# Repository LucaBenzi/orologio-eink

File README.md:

# Orologio E-Ink

E-ink desk clock with a 3.7" display, ESP32-C3 and LiFePO4 battery. Connects to WiFi, syncs time via NTP and runs for about 2 years on a single ~2-hour USB-C charge.

**Philosophy:** "Place it and it works. Recharge it every 2 years."

## Features

- 3.7" e-ink display (240x416 px) — sunlight readable, zero power draw at rest
- ESP32-C3 in deep sleep (~5 µA), wakes up every minute to update the display
- External 32.768 kHz crystal for accurate deep-sleep timekeeping (~1.7 s/day drift)
- Automatic nightly NTP sync to correct drift
- 2x LiFePO4 18650 cells in parallel (3600 mAh) — USB-C charging via TP5000
- Multiple battery chemistry support: LiFePO4, Li-Po, 3x AA alkaline (configurable via firmware and jumpers)
- WiFi setup via captive portal (WiFiManager) — no serial cable needed
- Automatic DST handling with IP geolocation
- Optional telemetry to Google Sheets (battery voltage, USB status, location)
- Custom PCB designed in KiCad and manufactured on JLCPCB

## Hardware

| Component | Model |
|---|---|
| MCU | ESP32-C3-MINI-1 |
| Display | WeAct Studio 3.7" e-Paper (GDEY037T03, driver UC8253) |
| Battery | 2x LiFePO4 18650 1800 mAh in parallel |
| Charger IC | TP5000 (CC/CV, cutoff 3.6 V) |
| LDO | MCP1700-330 |
| Connector | USB Type-C |
| Crystal | 32.768 kHz SMD 3215 |

Full pinout and circuit details are in [docs/specifiche.md](docs/specifiche.md).

## Repository structure

```
firmware/
  orologio_secondi.ino      # Arduino firmware (ESP32-C3)
  setup.html                 # WiFi configuration page (captive portal)
  telemetria_apps_script.js  # Google Apps Script for telemetry
pcb/
  progetto.kicad_pro         # KiCad 8 project
  progetto.kicad_sch         # schematic
  progetto.kicad_pcb         # PCB layout
  libs/                      # custom libraries and LCSC components
  loghi/                     # SVG logos on the board (CE, RoHS)
  production/                # Gerber, BOM, pick & place for JLCPCB
docs/
  specifiche.md              # full technical specifications
```

## Firmware setup

### Dependencies (Arduino IDE / PlatformIO)

- Board: `esp32` by Espressif (ESP32-C3)
- [GxEPD2](https://github.com/ZinggJM/GxEPD2)
- [U8g2_for_Adafruit_GFX](https://github.com/olikraus/U8g2_for_Adafruit_GFX)
- [WiFiManager](https://github.com/tzapu/WiFiManager)

### Battery configuration

In `orologio_secondi.ino`, uncomment the line matching the installed battery pack:

```cpp
#define BATTERIA_LIFEPO4    // LiFePO4 (default)
//#define BATTERIA_LIPO     // Li-Po / Li-ion
//#define BATTERIA_3AA      // 3x AA alkaline
```

This must match the jumper configuration on the PCB (JP_DIODE, JP_LDO, JP_CS).

### First boot

1. Power on the clock
2. Hold the button for 3 seconds
3. Connect your phone to the "orologio" WiFi network
4. Select your home WiFi and enter the password
5. The clock syncs via NTP and displays the time

## PCB

The KiCad project is in `pcb/`. The `production/` folder contains files ready for ordering on JLCPCB:

- `progetto.zip` — Gerber files
- `bom.csv` — Bill of Materials with LCSC part numbers
- `positions.csv` — pick & place file

## License

This project is open source. See the [LICENSE](LICENSE) file for details.

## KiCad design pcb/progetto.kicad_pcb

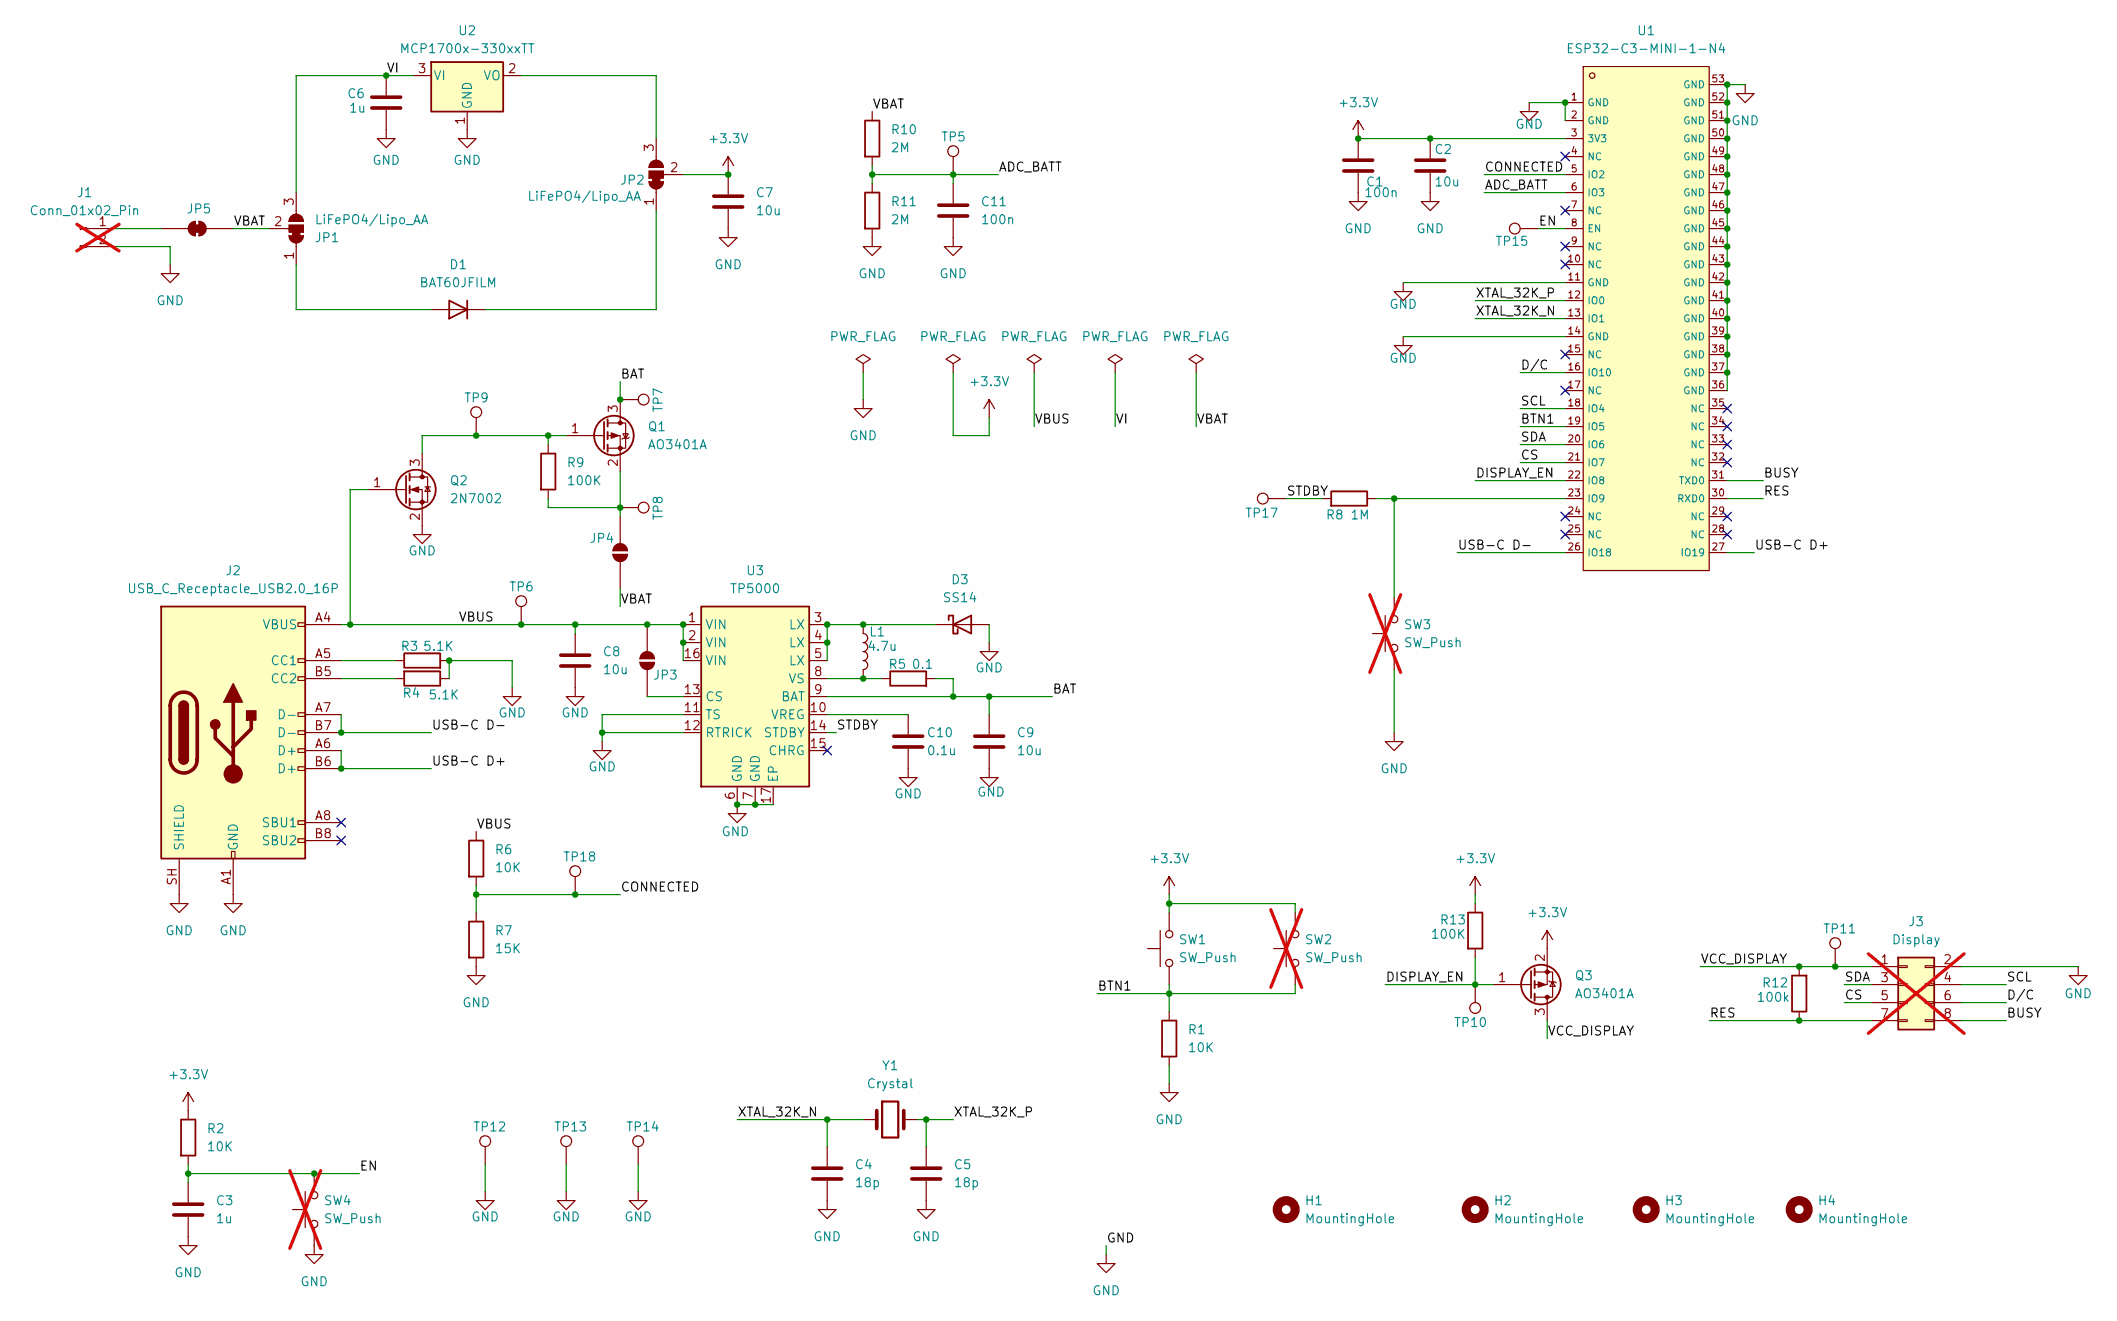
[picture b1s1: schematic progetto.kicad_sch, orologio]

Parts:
C1, C11: 100n; C_0402_1005Metric; LCSC C1525
C2, C7, C8, C9: 10u; C_0805_2012Metric; LCSC C15850
C3: 1u; C_0402_1005Metric; LCSC C52923
C4, C5: 18p; C_0402_1005Metric; LCSC C1549
C6: 1u; C_0603_1608Metric; LCSC C15849
C10: 0.1u; C_0402_1005Metric; LCSC C1525
D1: BAT60JFILM; D_SOD-323; LCSC C133103
D3: SS14; D_SMA; LCSC C2480
H1, H2, H3, H4: MountingHole; MountingHole_3.2mm_M3
J1: Conn_01x02_Pin; SolderWire-0.5sqmm_1x02_P4.6mm_D0.9mm_OD2.1mm; not fitted
J2: USB_C_Receptacle_USB2.0_16P; USB_C_Receptacle_HRO_TYPE-C-31-M-12; LCSC C165948
J3: Display; PinHeader_2x04_P2.54mm_Vertical; not fitted
JP1, JP2: LiFePO4/Lipo_AA; SolderJumper-3_P2.0mm_Open_TrianglePad1.0x1.5mm_NumberLabels
JP3, JP4: Lifepo4/Lipo; SolderJumper-2_P1.3mm_Open_RoundedPad1.0x1.5mm
JP5: SolderJumper_2_Bridged; SolderJumper-2_P1.3mm_Open_RoundedPad1.0x1.5mm
L1: 4.7u; L_Sunlord_SWPA5040S; LCSC C48496
Q1, Q3: AO3401A; SOT-23; LCSC C15127
Q2: 2N7002; SOT-23; LCSC C8545
R1, R2, R6: 10K; R_0402_1005Metric; LCSC C25744
R3, R4: 5.1K; R_0402_1005Metric; LCSC C25905
R5: 0.1; R_1206_3216Metric; LCSC C25334
R7: 15K; R_0402_1005Metric; LCSC C25756
R8: 1M; R_0402_1005Metric; LCSC C26083
R9, R13: 100K; R_0402_1005Metric; LCSC C25741
R10, R11: 2M; R_0603_1608Metric; LCSC C22976
R12: 100k; R_0402_1005Metric; LCSC C25741
SW1: SW_Push; SW_Tactile_SPST_Angled_PTS645Vx31-2LFS; LCSC C2804591
SW2, SW3, SW4: SW_Push; SW_SPST_TS-1088-xR020; not fitted
TP5, TP6, TP7, TP8, TP9, TP10, TP11, TP12, TP13, TP14, TP15, TP17, TP18: TestPoint; TestPoint_Pad_D1.5mm
U1: ESP32-C3-MINI-1-N4; C2838502_WIFIM-SMD_ESP32-C3-MINI-1; LCSC C2838502
U2: MCP1700x-330xxTT; SOT-23; LCSC C39051
U3: TP5000; QFN-16-1EP_4x4mm_P0.65mm_EP2.5x2.5mm; LCSC C51699
Y1: Crystal; Crystal_SMD_3215-2Pin_3.2x1.5mm; LCSC d3

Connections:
+3.3V: C1.1, C2.1, C7.1, JP2.2 (C), Q3.2 (S), R2.1, R13.1, SW1.2, SW2.2, U1.3 (3V3)
/ADC_BATT: C11.1, R10.2, R11.1, TP5.1 (1_1), U1.6 (IO3)
/BAT: C9.1, Q1.3 (D), R5.2, TP7.1 (1_1), U3.9 (BAT)
/BTN1: R1.1, SW1.1, SW2.1, U1.19 (IO5)
/BUSY: J3.8, U1.31 (TXD0)
/CONNECTED: R6.2, R7.1, TP18.1 (1_1), U1.5 (IO2)
/CS: J3.5, U1.21 (IO7)
/DISPLAY_EN: Q3.1 (G), R13.2, TP10.1 (1_1), U1.22 (IO8)
/D/C: J3.6, U1.16 (IO10)
/EN: C3.1, R2.2, SW4.2, TP15.1 (1_1), U1.8 (EN)
/RES: J3.7, R12.1, U1.30 (RXD0)
/SCL: J3.4, U1.18 (IO4)
/SDA: J3.3, U1.20 (IO6)
/STDBY: R8.2, TP17.1 (1_1), U3.14 (STDBY)
/USB-C D+: J2.A6 (D+), J2.B6 (D+), U1.27 (IO19)
/USB-C D-: J2.A7 (D-), J2.B7 (D-), U1.26 (IO18)
/VBAT: JP1.2 (C), JP4.2 (B), JP5.2 (B), R10.1
/VBUS: C8.1, J2.A4 (VBUS), J2.A9 (VBUS), J2.B4 (VBUS), J2.B9 (VBUS), JP3.2 (B), Q2.1 (G), R6.1, TP6.1 (1_1), U3.1 (VIN), U3.2 (VIN), U3.16 (VIN)
/VCC_DISPLAY: J3.1, Q3.3 (D), R12.2, TP11.1 (1_1)
/VI: C6.1, JP1.3 (B), U2.3 (VI)
/XTAL_32K_N: C4.1, U1.13 (IO1), Y1.1
/XTAL_32K_P: C5.1, U1.12 (IO0), Y1.2
GND: C1.2, C2.2, C3.2, C4.2, C5.2, C6.2, C7.2, C8.2, C9.2, C10.2, C11.2, D3.2 (A), J1.2, J2.A1 (GND), J2.A12 (GND), J2.B1 (GND), J2.B12 (GND), J2.SH (SHIELD), J3.2, Q2.2 (S), R1.2, R3.2, R4.1, R7.2, R11.2, SW3.1, SW4.1, TP12.1 (1_1), TP13.1 (1_1), TP14.1 (1_1), U1.1 (GND), U1.2 (GND), U1.11 (GND), U1.14 (GND), U1.36 (GND), U1.37 (GND), U1.38 (GND), U1.39 (GND), U1.40 (GND), U1.41 (GND), U1.42 (GND), U1.43 (GND), U1.44 (GND), U1.45 (GND), U1.46 (GND), U1.47 (GND), U1.48 (GND), U1.49 (GND), U1.50 (GND), U1.51 (GND), U1.52 (GND), U1.53 (GND), U2.1 (GND), U3.6 (GND), U3.7 (GND), U3.11 (TS), U3.12 (RTRICK), U3.17 (EP)
unnamed: D1.2 (A), JP1.1 (A)
unnamed: D1.1 (K), JP2.1 (A)
unnamed: D3.1 (K), L1.1, U3.3 (LX), U3.4 (LX), U3.5 (LX)
unnamed: J1.1, JP5.1 (A)
unnamed: J2.A5 (CC1), R3.1
unnamed: J2.B5 (CC2), R4.2
unnamed: JP2.3 (B), U2.2 (VO)
unnamed: JP3.1 (A), U3.13 (CS)
unnamed: JP4.1 (A), Q1.2 (S), R9.2, TP8.1 (1_1)
unnamed: Q1.1 (G), Q2.3 (D), R9.1, TP9.1 (1_1)
unnamed: R8.1, SW3.2, U1.23 (IO9)
unnamed: C10.1, U3.10 (VREG)
unnamed: L1.2, R5.1, U3.8 (VS)

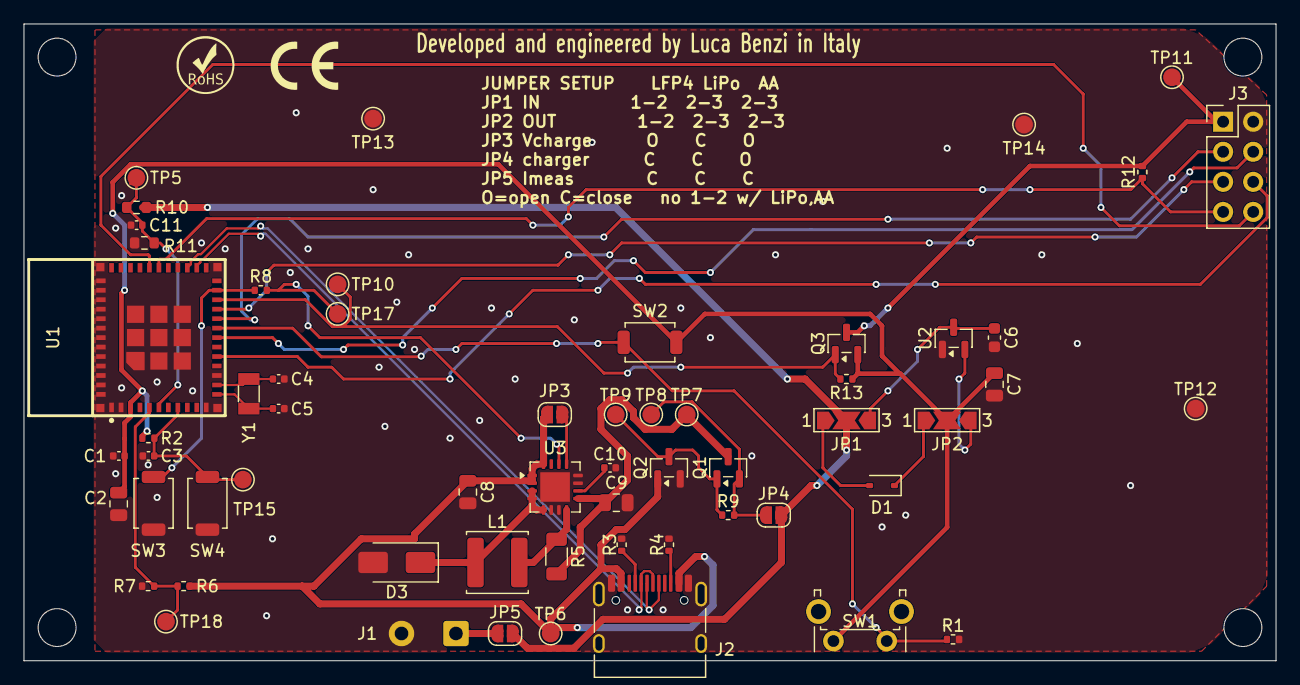
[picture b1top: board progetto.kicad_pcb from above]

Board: 2 copper layers, 105.8 x 53.8 mm, 63 parts (0 on the bottom side), 36 nets.

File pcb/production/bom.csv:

Designator,Footprint,Quantity,Value,LCSC Part #
"C1, C11",0402,2,100n,C1525
C10,0402,1,0.1u,C1525
"C2, C7, C8, C9",0805,4,10u,C15850
C3,0402,1,1u,C52923
"C4, C5",0402,2,18p,C1549
C6,0603,1,1u,C15849
D1,D_SOD-323,1,BAT60JFILM,C133103
D3,D_SMA,1,SS14,C2480
J2,USB_C_Receptacle_HRO_TYPE-C-31-M-12,1,USB_C_Receptacle_USB2.0_16P,C165948
L1,L_Sunlord_SWPA5040S,1,4.7u,C48496
"Q1, Q3",SOT-23,2,AO3401A,C15127
Q2,SOT-23,1,2N7002,C8545
"R1, R2, R6",0402,3,10K,C25744
"R10, R11",0603,2,2M,C22976
"R12, R13, R9",0402,3,100k,C25741
"R3, R4",0402,2,5.1K,C25905
R5,1206,1,0.1,C25334
R7,0402,1,15K,C25756
R8,0402,1,1M,C26083
SW1,SW_Tactile_SPST_Angled_PTS645Vx31-2LFS,1,SW_Push,C2804591
"TP10, TP11, TP12, TP13, TP14, TP15, TP17, TP18, TP5, TP6, TP7, TP8, TP9",TestPoint_Pad_D1.5mm,13,TestPoint,
U1,C2838502_WIFIM-SMD_ESP32-C3-MINI-1,1,ESP32-C3-MINI-1-N4,C2838502
U2,SOT-23,1,MCP1700x-330xxTT,C39051
U3,QFN-16-1EP_4x4mm_P0.65mm_EP2.5x2.5mm,1,TP5000,C51699
Y1,Crystal_SMD_3215-2Pin_3.2x1.5mm,1,Crystal,C32346

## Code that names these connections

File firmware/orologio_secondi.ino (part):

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
#define CS_PIN (SS)
#define BUSY_PIN (21)
#define RES_PIN (20)
#define DC_PIN (10)
#define BUTTON_PIN GPIO_NUM_5

#define PIN_BATTERIA 3
#define FW_VERSION "1.0"
#define PIN_USB 2
#define PIN_STDBY 9
#define PIN_DISPLAY_EN 8
#define TEMPO_ACCELERATO 40

// =======================================================
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// Q3 gate (AO3401A, P-ch): LOW = display powered, HIGH or hi-Z = off.
// R13 (100k to +3.3V) ensures cut-off when the ESP32 releases the pad.
#define ATTESA_RAIL_DISPLAY 50   // ms settling time for VCC_DISPLAY after turn-on
#define DURATA_RESET_DISPLAY 20  // ms pulse on RES: the UC8253 does a cold start
#define GOOGLE_SHEETS_URL "https://script.google.com/macros/s/AKfycbz1fNkQNdFf_IsT9enqTU-47g7L5uAMJDx-hzJf2sJf3KGpJOuUKP3DO-dTtvNoLfhJ/exec"

RTC_DATA_ATTR float tensioneBatteria = 0.0;
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  tensioneBatteria = adcMv * FATTORE_PARTITORE / 1000.0;
}

GxEPD2_BW<GxEPD2_370_GDEY037T03, GxEPD2_370_GDEY037T03::HEIGHT> display(GxEPD2_370_GDEY037T03(CS_PIN, DC_PIN, RES_PIN, BUSY_PIN));
U8G2_FOR_ADAFRUIT_GFX u8g2Fonts;

// -------------------------------------------------------
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  // Light sleep switches digital pads to their sleep configuration, which
  // defaults to hi-Z. On GPIO8 that would leave Q3's gate to R13, cutting
  // VCC_DISPLAY in the middle of a refresh. The hold freezes the level.
  gpio_hold_en((gpio_num_t)PIN_DISPLAY_EN);
  esp_light_sleep_start();
  gpio_hold_dis((gpio_num_t)PIN_DISPLAY_EN);
}

// Powers the panel and initializes it. Idempotent.
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void initDisplay(bool reset) {
  if (displayInizializzato) return;

  pinMode(PIN_DISPLAY_EN, OUTPUT);
  digitalWrite(PIN_DISPLAY_EN, LOW);
  // The pad must keep this configuration even during light sleep.
  gpio_sleep_sel_dis((gpio_num_t)PIN_DISPLAY_EN);
  displayAlimentato = true;
  delay(ATTESA_RAIL_DISPLAY);

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void spegniDisplay() {
  if (!displayAlimentato) {
    // Never turned on: leave the pad at hi-Z, R13 keeps Q3 in cut-off.
    pinMode(PIN_DISPLAY_EN, INPUT);
    return;
  }

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  // 3) Disconnect lines to the panel BEFORE cutting VCC, otherwise the ESP32
  //    back-powers it through the input protection diodes.
  SPI.end();
  pinMode(RES_PIN, INPUT);
  pinMode(DC_PIN, INPUT);
  pinMode(CS_PIN, INPUT);
  pinMode(BUSY_PIN, INPUT);

  // 4) Only now cut off Q3, driving the gate for a clean switch-off.
  gpio_hold_dis((gpio_num_t)PIN_DISPLAY_EN);
  digitalWrite(PIN_DISPLAY_EN, HIGH);
  delay(5);

  // 5) Release the pad. GPIO8 is not an RTC GPIO on the ESP32-C3, so in deep
  //    sleep it goes to hi-Z anyway: R13 guarantees the high level.
  pinMode(PIN_DISPLAY_EN, INPUT);

  displayAlimentato = false;
  displayInizializzato = false;
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  // on the same node). The internal pull-up is ~45k: in series with the megaohm
  // it would form a divider holding the pin at ~3.16V, and the low level would
  // never be detectable.
  pinMode(PIN_STDBY, INPUT);
  pinMode(PIN_USB, INPUT);

  leggiBatteria();
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      leggiBatteria();
      ultimaLettura = millis();

      if (!caricaCompleta && digitalRead(PIN_STDBY) == LOW) {
        caricaCompleta = true;
        // Close the animation on the full icon: without this call the last
        // drawn frame would stay on screen until the minute changes, and it
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void setup() {
  // Explicit initial state: pad at hi-Z, R13 keeps Q3 in cut-off.
  // The display stays disconnected until a path calls initDisplay().
  pinMode(PIN_DISPLAY_EN, INPUT);
  displayAlimentato = false;
  displayInizializzato = false;

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  // controller wakes up half-way and smears the screen grey. The ROM bootloader
  // drives GPIO21 as UART0 TX before our code even starts, so these lines must
  // be the first to run.
  pinMode(RES_PIN, INPUT);
  pinMode(DC_PIN, INPUT);
  pinMode(CS_PIN, INPUT);
  pinMode(BUSY_PIN, INPUT);
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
